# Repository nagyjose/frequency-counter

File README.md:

# High-Speed Frequency Counter & Pulse Shaper

> A high-speed digital frequency counter and pulse-shaping front-end module built around the Raspberry Pi Pico W (RP2040 MCU) and high-speed CMOS Schmitt triggers, equipped with a high-impedance JFET input buffer.

**Project Status:** `Completed / Hardware Design Ready` | **Main Technologies:** `Autodesk Eagle`, `Raspberry Pi Pico W (RP2040)`, `JFET / 74HC132`, `2-Layer PCB`

---

## 1. Overview & Key Features

The **Frequency Counter** module is designed for accurate measurement of signal frequency, period, and pulse intervals from RF and audio sources up to tens of megahertz. It features an active high-impedance analog front-end that conditions small or distorted analog waveforms into fast, clean logic edges suitable for hardware counting.

- **High-Impedance Front-End:** High-input-impedance JFET buffer (`MMBF5485`) minimizes capacitive and resistive loading on the signal source.
- **Overvoltage Protection:** Fast clamping diode network (`1N4148`, `RB751V40T1G`) protects the input stage against accidental overvoltage transients.
- **Adjustable Threshold / Sensitivity:** Multi-turn trimmer potentiometer (`POT1`, 500 Ω) adjusts the DC bias level across the level-shifting PNP transistor (`2N4403`) to optimize sensitivity for varying input amplitudes.
- **Fast Pulse Shaping:** High-speed quad NAND Schmitt trigger (`74HC132`) squares incoming signals into fast-rise digital pulses, with dedicated hardware gating / enable control.
- **RP2040 Dual-Core Processing:** Utilizes the Raspberry Pi Pico W for frequency counting via hardware PWM slice inputs / PIO state machines, enabling precise gated counting and wireless data transmission over Wi-Fi / BLE.
- **Flexible Power Management:** Automatic seamless power multiplexing between USB (`VBUS`) and an external terminal block (`VIN`, 5–12V) via a low-loss P-channel MOSFET (`DMG2305UX`) and Schottky diode (`STPS1L30`).
- **Rich Expansion Headers:** Dedicated connectors for `UART`, `I2C` (for OLED displays), `SPI`, and dual GPIO breakout headers (`JUM1`, `JUM2`).

---

## 2. Architecture & Operating Principle

```mermaid
flowchart LR
    subgraph AnalogFrontEnd["Analog Input & Signal Conditioning"]
        BNC["BNC Input<br/>(CON5)"] --> PROT["Protection Network<br/>(1N4148 Clamping)"]
        PROT --> JFET["JFET Buffer<br/>(MMBF5485)"]
        JFET --> PNP["Level Shifter & Bias<br/>(2N4403 + POT1 Trimmer)"]
    end

    subgraph PulseShaper["Digital Pulse Shaping"]
        PNP --> ST["74HC132 Schmitt Trigger<br/>(Quad 2-Input NAND)"]
        GATE["RP2040 Gate Control<br/>(GP13 / EN)"] --> ST
    end

    subgraph Controller["Digital Processing & Connectivity"]
        ST -->|"CLK-IN (GP12)"| PICO["Raspberry Pi Pico W<br/>(RP2040 Dual ARM Cortex-M0+)"]
        ST -->|"EDGE (GP14)"| PICO
        PICO --> UART["UART Port (CON1)<br/>Debug / Serial Stream"]
        PICO --> I2C["I2C Bus (CON4)<br/>OLED / Display"]
        PICO --> SPI["SPI Bus (CON3)<br/>Peripherals / Flash"]
        PICO --> WIFI["2.4 GHz Wi-Fi / BLE<br/>Wireless Telemetry"]
    end

    subgraph Power["Power Subsystem"]
        PWR_IN["Terminal (VIN) / USB (VBUS)"] --> PMOS["Power MUX (DMG2305UX)"]
        PMOS --> PICO
    end
```

### Signal Path Details
1. **Input Stage:** AC-coupled through `C1` into a high-impedance divider network (`R1`, `R2`) protected by back-to-back fast switching diodes `D1` and `D2`.
2. **Buffer & Level Shift:** JFET `M1` acts as a high-impedance voltage buffer, driving PNP transistor `Q2`. Trimmer `POT1` allows fine-tuning the operating point to capture both small AC signals (<100 mVpp) and rail-to-rail digital logic.
3. **Schmitt Triggering:** The conditioned signal is AC-coupled via `C5` into `IC1` (`74HC132`). The Schmitt trigger provides sharp hysteresis and eliminates false triggering on noisy or slow edges.
4. **RP2040 Capture:** The pulse stream is routed to `GP12` (`CLK-IN`) and `GP14` (`EDGE`). The RP2040 PWM counters or PIO state machines count input pulses over calibrated gate times generated by hardware timers.

---

## 3. Schematic & Hardware Previews

### Circuit Schematic

📄 [Open original high-resolution schematic drawing (PDF)](Freq-counter.pdf)

---

## 4. Project Structure

```text
.
├── Freq-counter.sch             # Autodesk Eagle schematic
├── Freq-counter.brd             # Autodesk Eagle 2-layer PCB layout (~77 x 57 mm)
├── Freq-counter.pdf             # Exported schematic reference drawing
├── eagle.epf                    # Eagle project configuration
├── Freq-counter_2025-07-29.zip  # Production package (CAM Gerber & Drill files, PnP assembly)
├── docs/
│   └── images/
│       └── schematic_p1.png     # Rendered high-resolution schematic preview
├── .gitignore                   # Ignore Eagle backup and temporary files
└── README.md                    # Project documentation
```

### Production Gerber & Drill Package (`Freq-counter_2025-07-29.zip`)
Contains standard RS-274X Gerber files and Excellon NC drill files ready for fabrication (JLCPCB, PCBWay, etc.):
- `copper_top.gbr`, `copper_bottom.gbr`
- `soldermask_top.gbr`, `soldermask_bottom.gbr`
- `silkscreen_top.gbr`, `silkscreen_bottom.gbr`
- `drill_1_16.xln`, `profile.gbr`
- `PnP_Freq-counter_front.txt`, `PnP_Freq-counter_back.txt` (Pick and Place)

---

## 5. Hardware Specifications & Pinout

### Technical Specifications
| Parameter | Value | Notes |
| :--- | :--- | :--- |
| **Microcontroller** | Raspberry Pi Pico W (RP2040) | Dual-core ARM Cortex-M0+ @ 133 MHz |
| **Input Connector** | BNC Female (`CON5`) | Standard 50 Ω / 1 MΩ scope probe compatible |
| **Input Coupling** | AC-coupled | `C1` (1 µF) capacitor |
| **Input Buffer** | MMBF5485 JFET | N-channel RF amplifier / high-Z buffer |
| **Pulse Shaper** | 74HC132 | Quad 2-input NAND Schmitt trigger |
| **Operating Voltage** | 5V DC (USB or Terminal) | Onboard 3.3V LDO on Pico W powers logic |
| **PCB Dimensions** | ~77.1 mm × 57.2 mm | 2 layers, FR4, 1.6 mm thickness |
| **Mounting** | 4 × M3 mounting holes (`H1`–`H4`) | Grounded / chassis connection |

### Raspberry Pi Pico Pin Mapping
| Pico Pin | Net Name | Function / Description |
| :--- | :--- | :--- |
| **GP12** | `CLK-IN` | High-speed pulse input from 74HC132 shaper |
| **GP14** | `EDGE` | Alternate edge detection input |
| **GP13** | `EN` | Hardware gate / enable line to 74HC132 |
| **GP0 / GP1** | `UART0-TX / RX` | Dedicated serial interface (`CON1`) |
| **GP4 / GP5** | `I2C0-SDA / SCK` | I2C bus with 4.7 kΩ pull-ups (`CON4`) |
| **GP16..GP19**| `SPI0-MISO/CS/SCK/MOSI` | High-speed SPI peripheral header (`CON3`) |
| **GP2..GP11** | `GPIO-0` .. `GPIO-7` | Breakout jumper header `JUM1` (8 pins) |
| **GP20..GP28**| `GPIO-8` .. `GPIO-13` | Breakout jumper header `JUM2` (6 pins) |

---

## 6. Getting Started & Fabrication

### PCB Ordering
Upload `Freq-counter_2025-07-29.zip` to any standard PCB manufacturer:
- **Layers:** 2
- **Dimensions:** 77.1 mm × 57.2 mm
- **Surface Finish:** HASL lead-free or ENIG (recommended for SMT components)
- **Solder Mask:** Green (or preferred color)
- **Copper Weight:** 1 oz (35 µm)

### Calibration & Tuning
1. Apply 5V power via the `CON2` screw terminal or USB port on the Raspberry Pi Pico.
2. Connect a function generator set to 1 MHz sine wave (1 Vpp) to the BNC input `CON5`.
3. Monitor the output of the Schmitt trigger on `GP12` (`CLK-IN`) with an oscilloscope.
4. Adjust trimmer potentiometer `POT1` until a symmetrical 50% duty cycle square wave is observed at `GP12`.
5. Verify that `GP13` (`EN`) set to LOW disables pulse transmission to the counter.

---

## 7. Related Projects

This board is part of a measurement and embedded instrumentation hardware suite:
- **[Oscilloscope Front-End](../Oscilloscope-front-end/):** Wideband analog front-end with programmable attenuator, AC/DC coupling, and high-speed ADC.
- **[rpi_pico](../../CVUT/projekty/rpi_pico/):** MicroPython firmware examples for Raspberry Pi Pico W (BLE, MQTT, wireless sensor communication).

---

## 8. Project Status & Next Steps

- [x] Schematic design and simulation of JFET buffer.
- [x] Complete 2-layer PCB layout with ground planes.
- [x] Generation of manufacturing Gerber and Drill outputs (`2025-07-29`).
- [ ] Firmware development: High-speed reciprocal frequency counter using RP2040 PIO state machines.
- [ ] 3D printable enclosure design.

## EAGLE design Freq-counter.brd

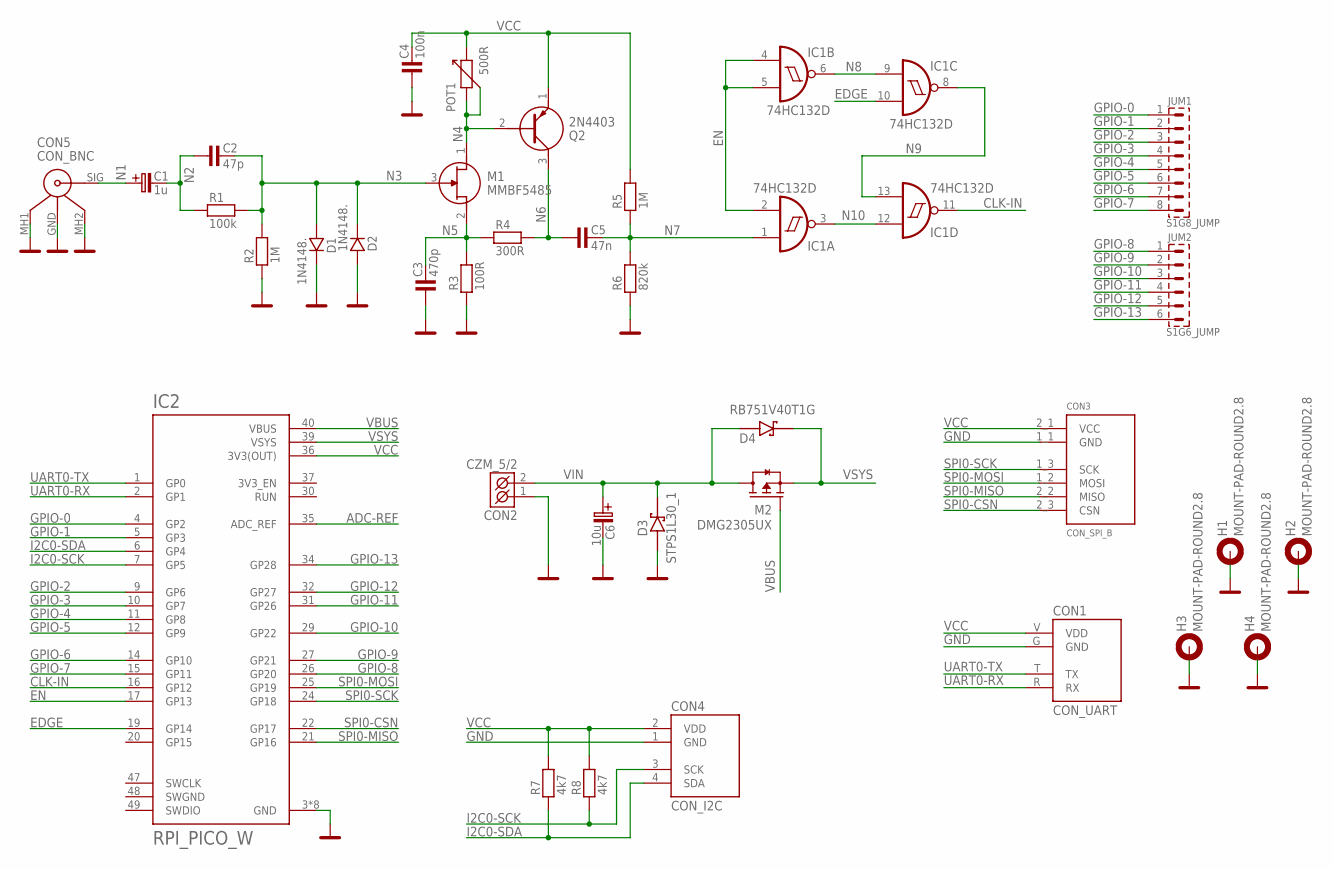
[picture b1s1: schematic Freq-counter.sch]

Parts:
C1: 1u; C_EL-SMD_B
C2: 47p; 0805
C3: 470p; 0805
C4: 100n; 0805
C5: 47n; 0805
C6: 10u; C_EL-SMD_D
CON1: CON_UART; UART_CONN
CON2: CZM_5/2
CON3: CON_SPI_B; SPI_CONN_2
CON4: CON_I2C; I2C_CONN
CON5: CON_BNC; CPBNCPC010
D1, D2: 1N4148.; SOD-80
D3: STPS1L30_1; SMA
D4: RB751V40T1G; SOD323
H1, H2, H3, H4: MOUNT-PAD-ROUND2.8; 2,8-PAD
IC1: 74HC132D; SO14
IC2: RPI_PICO_W
JUM1: S1G8_JUMP; S1G8_JUM
JUM2: S1G6_JUMP; S1G6_JUM
M1: MMBF5485; SOT96P237X111-3N
M2: DMG2305UX; TRANSISTOR-FET_SOT23
POT1: 500R; POT
Q2: 2N4403; CS_TO-92
R1: 100k; 0805
R2, R5: 1M; 0805
R3: 100R; 0805
R4: 300R; 0805
R6: 820k; 0805
R7, R8: 4k7; 0805

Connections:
ADC-REF: IC2.35 (ADC_REF)
CLK-IN: IC1.11 (O), IC2.16 (GP12)
EDGE: IC1.10 (I1), IC2.19 (GP14)
EN: IC1.2 (I1), IC1.4 (I0), IC1.5 (I1), IC2.17 (GP13)
GND: C3.1, C4.1, C6.- (C_EL-), CON1.G (GND), CON2.1 (K1), CON3.1_1 (GND), CON4.1 (GND), CON5.MH1, CON5.MH2, D1.K, D2.A, D3.2 (A), H1.B2,8, H2.B2,8, H3.B2,8, H4.B2,8, IC1.7 (GND), IC2.3 (GND), IC2.8 (GND), IC2.13 (GND), IC2.18 (GND), IC2.23 (GND), IC2.28 (GND), IC2.33 (GND), IC2.38 (GND), R2.1, R3.1, R6.1
GPIO-0: IC2.4 (GP2), JUM1.1
GPIO-1: IC2.5 (GP3), JUM1.2
GPIO-2: IC2.9 (GP6), JUM1.3
GPIO-3: IC2.10 (GP7), JUM1.4
GPIO-4: IC2.11 (GP8), JUM1.5
GPIO-5: IC2.12 (GP9), JUM1.6
GPIO-6: IC2.14 (GP10), JUM1.7
GPIO-7: IC2.15 (GP11), JUM1.8
GPIO-8: IC2.26 (GP20), JUM2.1
GPIO-9: IC2.27 (GP21), JUM2.2
GPIO-10: IC2.29 (GP22), JUM2.3
GPIO-11: IC2.31 (GP26), JUM2.4
GPIO-12: IC2.32 (GP27), JUM2.5
GPIO-13: IC2.34 (GP28), JUM2.6
I2C0-SCK: CON4.3 (SCK), IC2.7 (GP5), R8.1
I2C0-SDA: CON4.4 (SDA), IC2.6 (GP4), R7.1
N1: C1.+ (C_EL+), CON5.SIG
N2: C1.- (C_EL-), C2.1, R1.1
N3: C2.2, D1.A, D2.K, M1.3 (G), R1.2, R2.2
N4: M1.1 (D), POT1.1, POT1.2, Q2.2 (B)
N5: C3.2, M1.2 (S), R3.2, R4.1
N6: C5.1, Q2.3 (C), R4.2
N7: C5.2, IC1.1 (I0), R5.1, R6.2
N8: IC1.6 (O), IC1.9 (I0)
N9: IC1.8 (O), IC1.13 (I1)
N10: IC1.3 (O), IC1.12 (I0)
SPI0-CSN: CON3.2_3 (CSN), IC2.22 (GP17)
SPI0-MISO: CON3.2_2 (MISO), IC2.21 (GP16)
SPI0-MOSI: CON3.1_2 (MOSI), IC2.25 (GP19)
SPI0-SCK: CON3.1_3 (SCK), IC2.24 (GP18)
SWGND: IC2.48 (SWGND)
UART0-RX: CON1.R (RX), IC2.2 (GP1)
UART0-TX: CON1.T (TX), IC2.1 (GP0)
VBUS: IC2.40 (VBUS), M2.1 (G)
VCC: C4.2, CON1.V (VDD), CON3.2_1 (VCC), CON4.2 (VDD), IC1.14 (VCC), IC2.36 (3V3(OUT)), POT1.3, Q2.1 (E), R5.2, R7.2, R8.2
VIN: C6.+ (C_EL+), CON2.2 (K2), D3.1 (C), D4.2 (A), M2.3 (D)
VSYS: D4.1 (C), IC2.39 (VSYS), M2.2 (S)

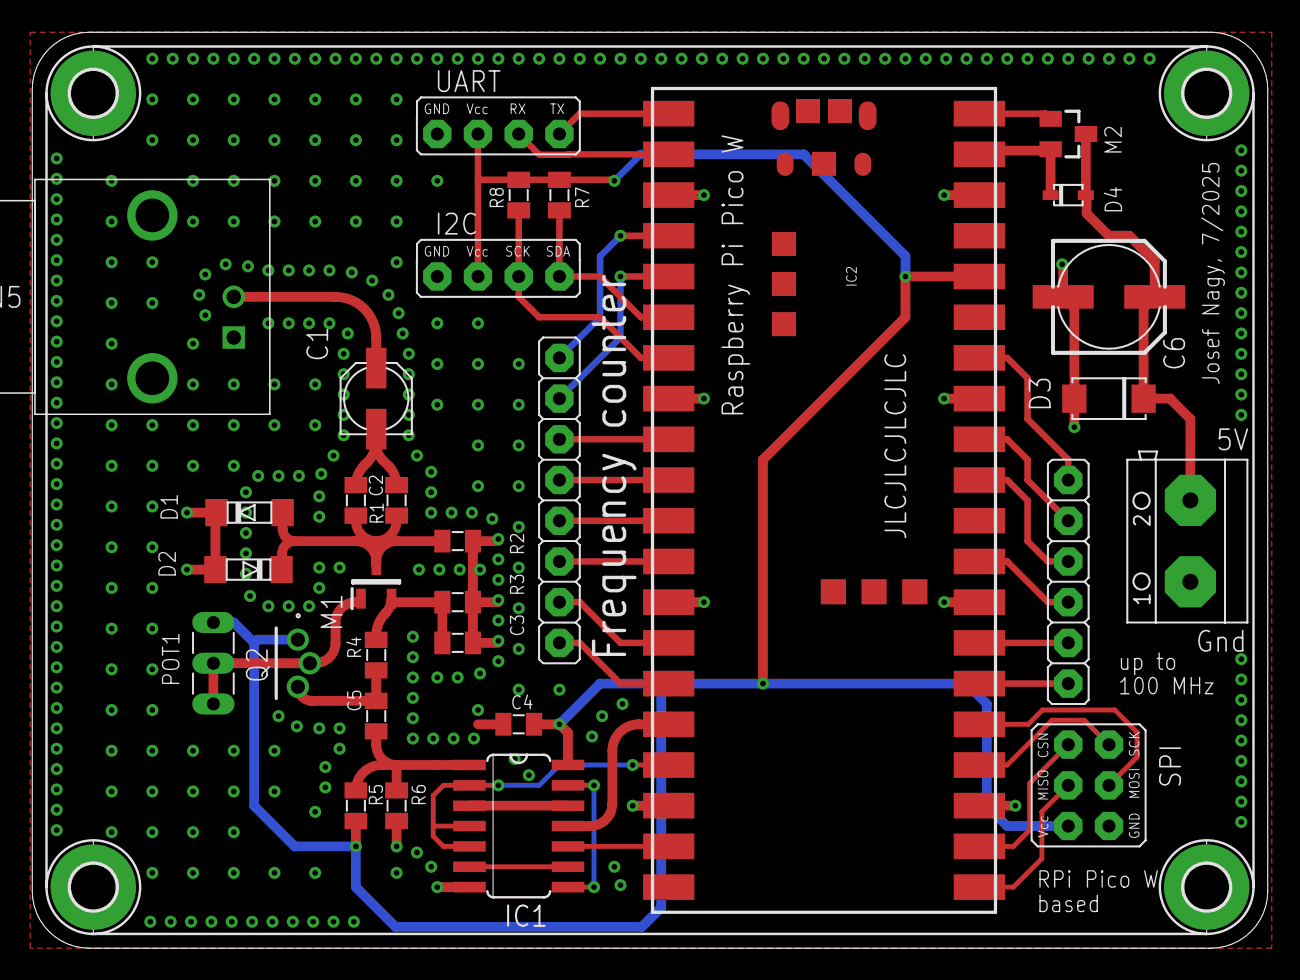
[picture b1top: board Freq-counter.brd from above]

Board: 2 copper layers, 77.1 x 57.1 mm, 35 parts (0 on the bottom side), 40 nets.

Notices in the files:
parts and their libraries:
Copyright (C) PaJa 2011-2014
Copyright (C) PaJa 2001-2014
